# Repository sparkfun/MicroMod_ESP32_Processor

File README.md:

SparkFun MicroMod ESP32 Processor Board
========================================

[*SparkFun MicroMod ESP32 Processor Board (16781)*](https://www.sparkfun.com/products/16781)

The MicroMod ESP32 Processor Board combines Espressif's ESP32 with our M.2 connector interface to bring a power-packed processor board into our MicroMod ecosystem. 

The ESP32 includes a laundry list of functionality, including the dual-core Tensilica LX6 microprocessor, 240MHz clock frequency, 520kB internal SRAM, integrated WiFi transceiver, and hardware accelerated encryption (AES, SHA2, ECC, RSA-4096). With this MicroMod processor board, you have access to 8 general use IO pins, dedicated analog, digital, and PWM pins, as well as all the fan favorites - SPI, I<sup>2</sup>C, UART, and SDIO. Add to that 16MB flash storage and sleep current of around 500&micro;A, and you've got a perfect storm of versatility. 

Grab yourself a SparkFun MicroMod ESP32 Processor Board and a compatible carrier board and get to hacking! 

Repository Contents
-------------------

* **/Documentation** - Data sheets, additional product information
* **/Hardware** - Eagle design files (.brd, .sch)
* **/Production** - Production panel files (.brd)

Documentation
--------------
* **[Hookup Guide](https://learn.sparkfun.com/tutorials/micromod-esp32-processor-board-hookup-guide)** - Basic hookup guide for the SparkFun MicroMod ESP32 Processor Board.
* **[Getting Started with MicroMod](https://learn.sparkfun.com/tutorials/getting-started-with-micromod)** - A tutorial to help you get started with the MicroMod Ecosystem. 
* **[Designing with MicroMod](https://learn.sparkfun.com/tutorials/designing-with-micromod)** - A tutorial to walk you through the specs of the MicroMod processor and carrier board as well as the basics of incorporating the MicroMod form factor into your own PCB designs.

License Information
-------------------

This product is _**open source**_! 

Please review the LICENSE.md file for license information. 

If you have any questions or concerns on licensing, please contact technical support on our [SparkFun forums](https://forum.sparkfun.com/viewforum.php?f=152).

Distributed as-is; no warranty is given.

- Your friends at SparkFun.

_<COLLABORATION CREDIT>_

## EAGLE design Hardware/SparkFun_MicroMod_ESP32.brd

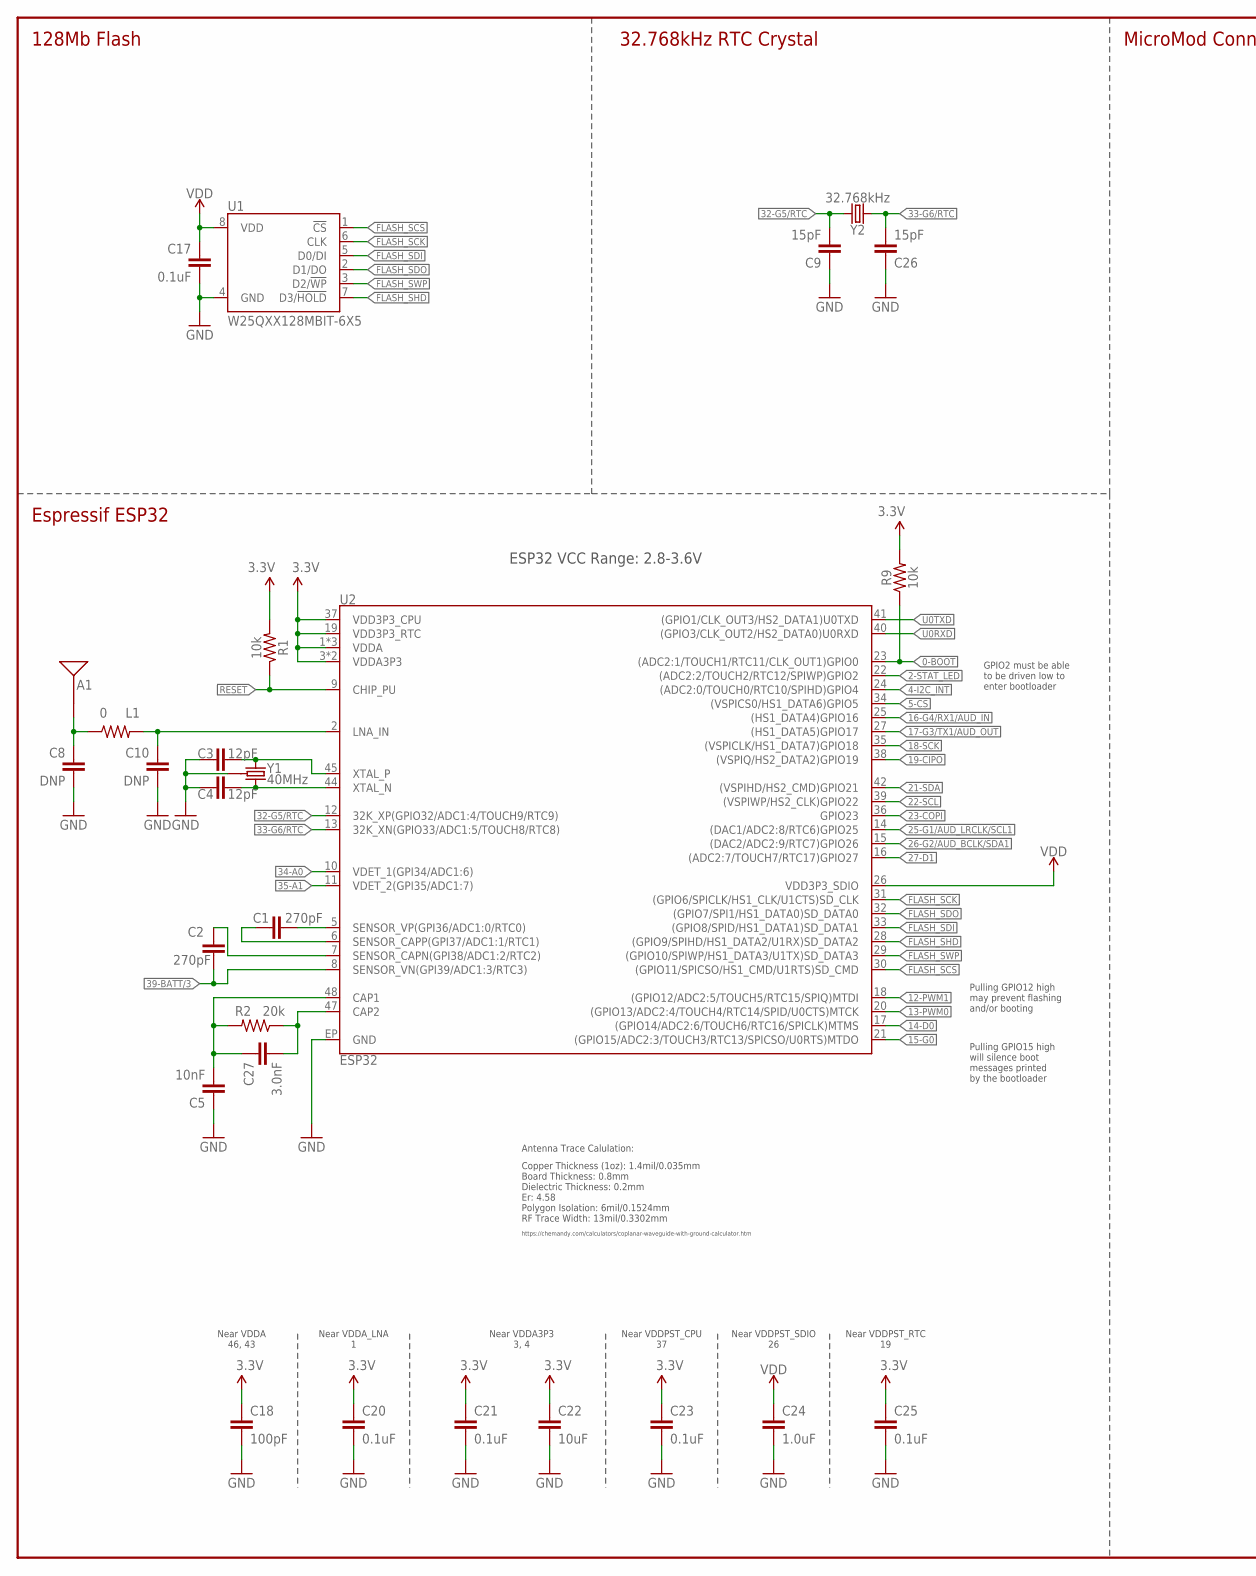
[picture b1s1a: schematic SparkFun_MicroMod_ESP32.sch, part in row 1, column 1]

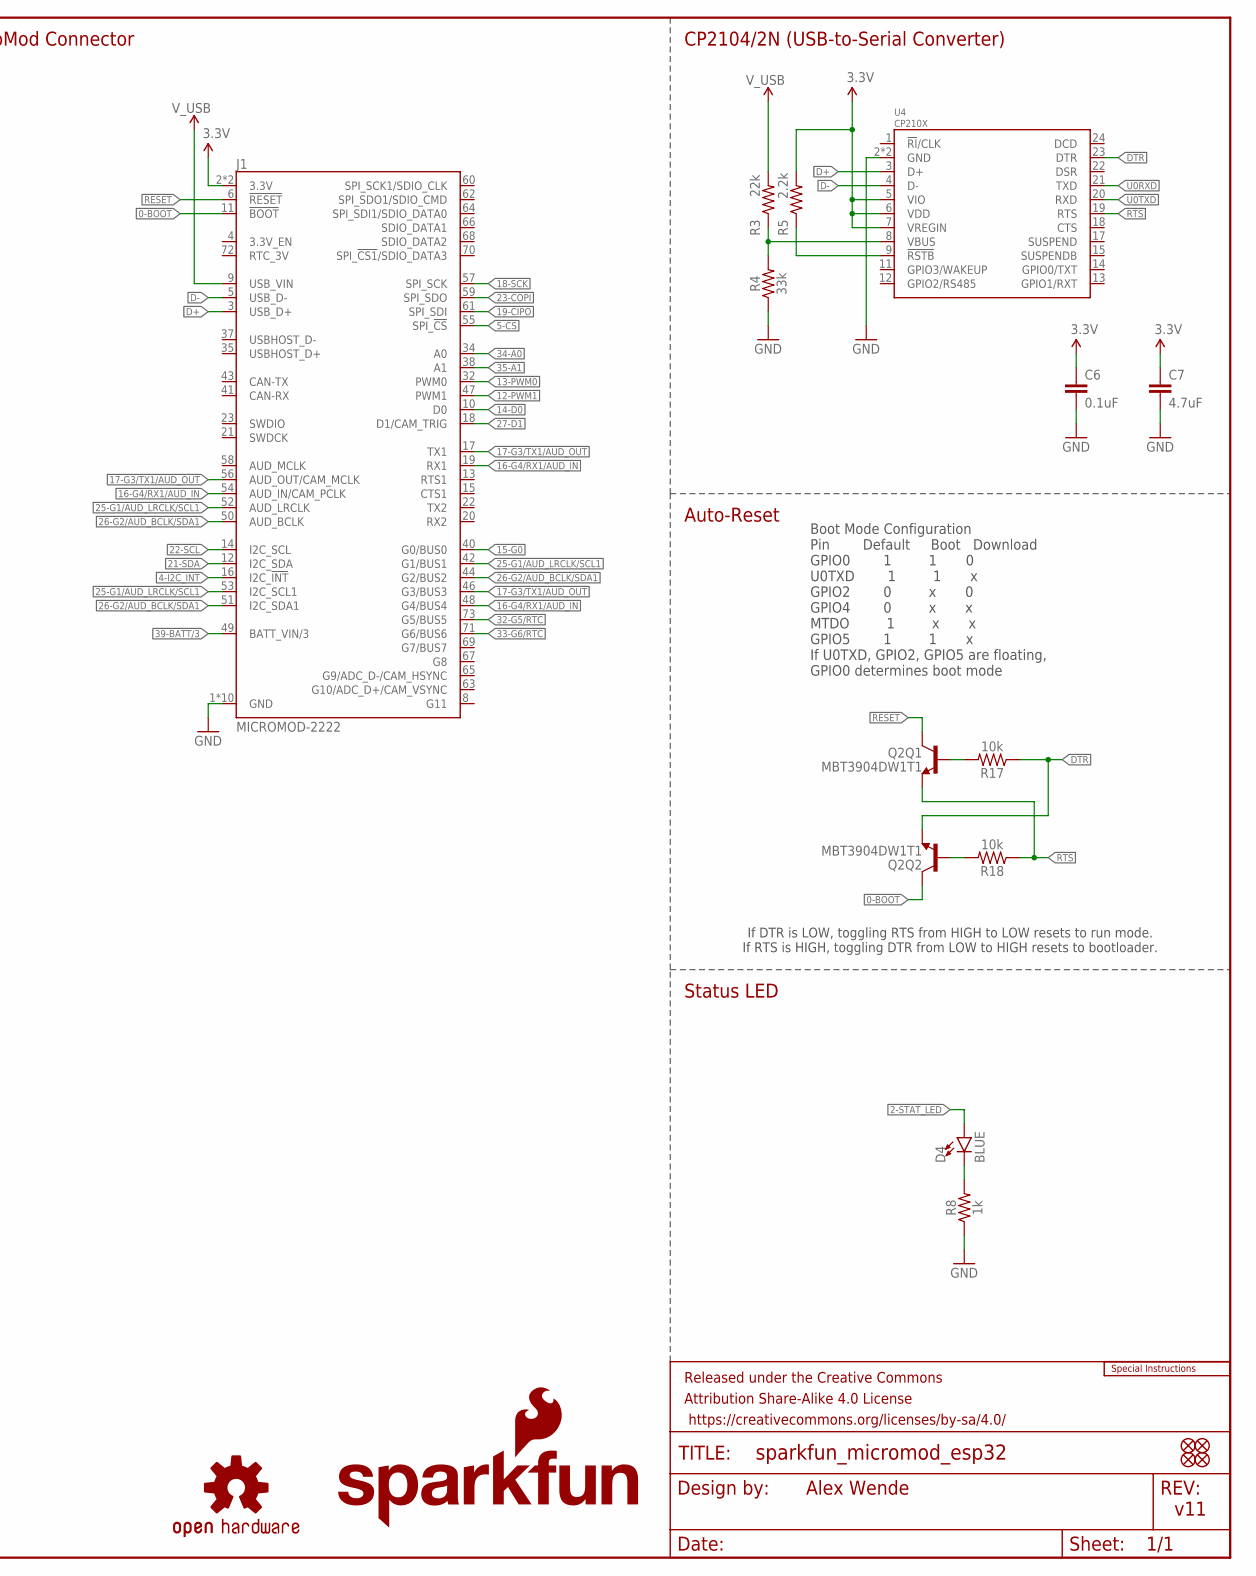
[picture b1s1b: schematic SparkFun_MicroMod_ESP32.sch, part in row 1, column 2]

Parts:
A1: ANTENNA2.4GHZ-8.0X1.0MM; ANT-2.4GHZ-8.0X1.0MM
C1, C2: 270pF; 0402-TIGHT
C3, C4: 12pF; 0402-TIGHT
C5: 10nF; 0402-TIGHT
C6, C17, C20, C21, C23, C25: 0.1uF; 0402-TIGHT
C7: 4.7uF; 0402-TIGHT
C8, C10: DNP; 0402-TIGHT
C9, C26: 15pF; 0402-TIGHT
C18: 100pF; 0402-TIGHT
C22: 10uF; 0402-TIGHT
C24: 1.0uF; 0402-TIGHT
C27: 3.0nF; 0402-TIGHT
D4: BLUE; LED-0603
FD1, FD2, FD3, FD4: FIDUCIALUFIDUCIAL; FIDUCIAL-MICRO
FRAME1: FRAME-LEDGER; CREATIVE_COMMONS
J1: MICROMOD-2222; M.2-CARD-E-22
L1: 0; 0402-TIGHT
LOGO1: SPECIAL_INSTRUCTIONS-ORDERING; ORDERING_INSTRUCTIONS
LOGO2: SFE_LOGO_NAME_FLAME.1_INCH; SFE_LOGO_NAME_FLAME_.1
LOGO3: OSHW-LOGOS; OSHW-LOGO-S
Q2: MBT3904DW1T1; SC70-6
R1, R9, R17, R18: 10k; 0402-TIGHT
R2: 20k; 0402-TIGHT
R3: 22k; 0402-TIGHT
R4: 33k; 0402-TIGHT
R5: 2.2k; 0402-TIGHT
R8: 1k; 0402-TIGHT
U1: W25QXX128MBIT-6X5; WSON-8-6X5
U2: ESP32; QFN48-0.4MM
U4: CP210X; QFN24
Y1: 40MHz; CRYSTAL-SMD-2X2.5MM
Y2: 32.768kHz; CRYSTAL-SMD-3.2X1.5MM

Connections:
0-!BOOT!: J1.11 (!BOOT!), Q2.6 (C), R9.1, U2.23 ((ADC2:1/TOUCH1/RTC11/CLK_OUT1)GPIO0)
2-STAT_LED: D4.A, U2.22 ((ADC2:2/TOUCH2/RTC12/SPIWP)GPIO2)
3.3V: C6.1, C7.1, C18.1, C20.1, C21.1, C22.1, C23.1, C25.1, J1.2 (3.3V), J1.74 (3.3V), R1.2, R5.2, R9.2, U2.1 (VDDA), U2.3 (VDDA3P3), U2.4 (VDDA3P3), U2.19 (VDD3P3_RTC), U2.37 (VDD3P3_CPU), U2.43 (VDDA), U2.46 (VDDA), U4.5 (VIO), U4.6 (VDD), U4.7 (VREGIN)
4-I2C_!INT: J1.16 (I2C_!INT!), U2.24 ((ADC2:0/TOUCH0/RTC10/SPIHD)GPIO4)
5-!CS: J1.55 (SPI_!CS!), U2.34 ((VSPICS0/HS1_DATA6)GPIO5)
12-PWM1: J1.47 (PWM1), U2.18 ((GPIO12/ADC2:5/TOUCH5/RTC15/SPIQ)MTDI)
13-PWM0: J1.32 (PWM0), U2.20 ((GPIO13/ADC2:4/TOUCH4/RTC14/SPID/U0CTS)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)
14-D0: J1.10 (D0), U2.17 ((GPIO14/ADC2:6/TOUCH6/RTC16/SPICLK)MTMS)
15-G0: J1.40 (G0/BUS0), U2.21 ((GPIO15/ADC2:3/TOUCH3/RTC13/SPICSO/U0RT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)
16-G4/RX1/AUD_IN: J1.19 (RX1), J1.48 (G4/BUS4), J1.54 (AUD_IN/CAM_PCLK), U2.25 ((HS1_DATA4)GPIO16)
17-G3/TX1/AUD_OUT: J1.17 (TX1), J1.46 (G3/BUS3), J1.56 (AUD_OUT/CAM_MCLK), U2.27 ((HS1_DATA5)GPIO17)
18-SCK: J1.57 (SPI_SCK), U2.35 ((VSPICLK/HS1_DATA7)GPIO18)
19-CIPO: J1.61 (SPI_SDI), U2.38 ((VSPIQ/HS2_DATA2)GPIO19)
21-SDA: J1.12 (I2C_SDA), U2.42 ((VSPIHD/HS2_CMD)GPIO21)
22-SCL: J1.14 (I2C_SCL), U2.39 ((VSPIWP/HS2_CLK)GPIO22)
23-COPI: J1.59 (SPI_SDO), U2.36 (GPIO23)
25-G1/AUD_LRCLK/SCL1: J1.42 (G1/BUS1), J1.52 (AUD_LRCLK), J1.53 (I2C_SCL1), U2.14 ((DAC1/ADC2:8/RTC6)GPIO25)
26-G2/AUD_BCLK/SDA1: J1.44 (G2/BUS2), J1.50 (AUD_BCLK), J1.51 (I2C_SDA1), U2.15 ((DAC2/ADC2:9/RTC7)GPIO26)
27-D1: J1.18 (D1/CAM_TRIG), U2.16 ((ADC2:7/TOUCH7/RTC17)GPIO27)
32-G5/RTC: C9.2, J1.73 (G5/BUS5), U2.12 (32K_XP(GPIO32/ADC1:4/TOUCH9/RTC9)), Y2.P$1 (1)
33-G6/RTC: C26.2, J1.71 (G6/BUS6), U2.13 (32K_XN(GPIO33/ADC1:5/TOUCH8/RTC8)), Y2.P$2 (2)
34-A0: J1.34 (A0), U2.10 (VDET_1(GPI34/ADC1:6))
35-A1: J1.38 (A1), U2.11 (VDET_2(GPI35/ADC1:7))
36: C1.2, U2.5 (SENSOR_VP(GPI36/ADC1:0/RTC0))
37: C1.1, U2.6 (SENSOR_CAPP(GPI37/ADC1:1/RTC1))
38: C2.1, U2.7 (SENSOR_CAPN(GPI38/ADC1:2/RTC2))
39-BATT/3: C2.2, J1.49 (BATT_VIN/3), U2.8 (SENSOR_VN(GPI39/ADC1:3/RTC3))
!RESET: J1.6 (!RESET!), Q2.3 (C), R1.1, U2.9 (CHIP_PU)
CAP_10N: C5.2, C27.1, R2.2, U2.48 (CAP1)
D+: J1.3 (USB_D+), U4.3 (D+)
D-: J1.5 (USB_D-), U4.4 (D-)
DTR: Q2.1 (E), R17.1, U4.23 (DTR)
FLASH_SCK: U1.6 (CLK), U2.31 ((GPIO6/SPICLK/HS1_CLK/U1CTS)SD_CLK)
FLASH_SCS: U1.1 (!CS!), U2.30 ((GPIO11/SPICSO/HS1_CMD/U1RTS)SD_CMD)
FLASH_SDI: U1.5 (D0/DI), U2.33 ((GPIO8/SPID/HS1_DATA1)SD_DATA1)
FLASH_SDO: U1.2 (D1/DO), U2.32 ((GPIO7/SPI1/HS1_DATA0)SD_DATA0)
FLASH_SHD: U1.7 (D3/!HOLD!), U2.28 ((GPIO9/SPIHD/HS1_DATA2/U1RX)SD_DATA2)
FLASH_SWP: U1.3 (D2/!WP!), U2.29 ((GPIO10/SPIWP/HS1_DATA3/U1TX)SD_DATA3)
GND: C3.1, C4.1, C5.1, C6.2, C7.2, C8.2, C9.1, C10.2, C17.2, C18.2, C20.2, C21.2, C22.2, C23.2, C24.2, C25.2, C26.1, J1.1 (GND), J1.7 (GND), J1.33 (GND), J1.36 (GND), J1.39 (GND), J1.45 (GND), J1.75 (GND), J1.GND1 (GND), J1.GND2 (GND), J1.GND3 (GND), R4.1, R8.1, U1.4 (GND), U2.EP (GND), U4.2 (GND), U4.PAD (GND), Y1.P2 (GND), Y1.P4 (GND)
unnamed: D4.C, R8.2
unnamed: R3.1, R4.2, U4.8 (VBUS)
unnamed: R5.1, U4.9 (!RSTB)
unnamed: C27.2, R2.1, U2.47 (CAP2)
unnamed: A1.FEED, C8.1, L1.1
unnamed: C10.1, L1.2, U2.2 (LNA_IN)
unnamed: Q2.5 (B), R17.2
unnamed: Q2.2 (B), R18.2
unnamed: C3.2, U2.45 (XTAL_P), Y1.P1 (1)
unnamed: C4.2, U2.44 (XTAL_N), Y1.P3 (2)
RTS: Q2.4 (E), R18.1, U4.19 (RTS)
U0RXD: U2.40 ((GPIO3/CLK_OUT2/HS2_DATA0)U0RXD), U4.21 (TXD)
U0TXD: U2.41 ((GPIO1/CLK_OUT3/HS2_DATA1)U0TXD), U4.20 (RXD)
VDD: C17.1, C24.1, U1.8 (VDD), U2.26 (VDD3P3_SDIO)
V_USB: J1.9 (USB_VIN), R3.2

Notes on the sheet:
Boot Mode Configuration Pin Default Boot Download GPIO0 1 1 0 U0TXD 1 1 x GPIO2 0 x 0 GPIO4 0 x x MTDO 1 x x GPIO5 1 1 x If U0TXD, GPIO2, GPIO5 are floating, GPIO0 determines boot mode
Auto-Reset
Near VDDA 46, 43
Near VDDA_LNA 1
Near VDDA3P3 3, 4
Near VDDPST_CPU 37
Near VDDPST_SDIO 26
Near VDDPST_RTC 19
Espressif ESP32
128Mb Flash
32.768kHz RTC Crystal
Status LED
v11
Alex Wende
ESP32 VCC Range: 2.8-3.6V
If DTR is LOW, toggling RTS from HIGH to LOW resets to run mode. If RTS is HIGH, toggling DTR from LOW to HIGH resets to bootloader.
CP2104/2N (USB-to-Serial Converter)
MicroMod Connector
Antenna Trace Calulation:
Copper Thickness (1oz): 1.4mil/0.035mm Board Thickness: 0.8mm Dielectric Thickness: 0.2mm Er: 4.58 Polygon Isolation: 6mil/0.1524mm RF Trace Width: 13mil/0.3302mm
https://chemandy.com/calculators/coplanar-waveguide-with-ground-calculator.htm
GPIO2 must be able to be driven low to enter bootloader
Pulling GPIO12 high may prevent flashing and/or booting
Pulling GPIO15 high will silence boot messages printed by the bootloader

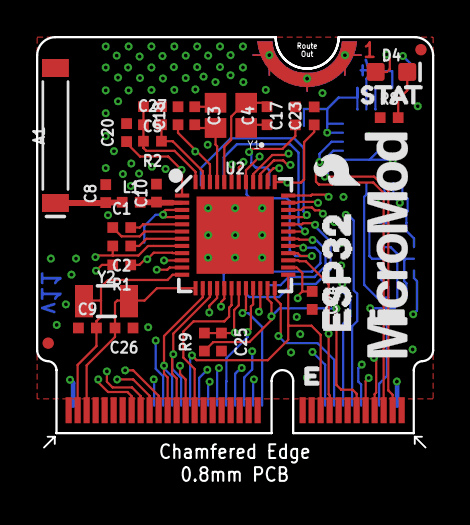
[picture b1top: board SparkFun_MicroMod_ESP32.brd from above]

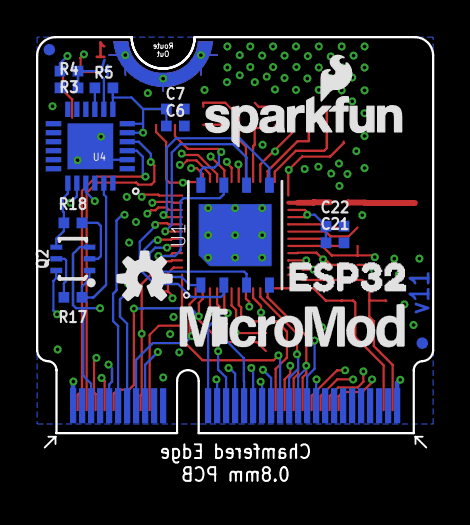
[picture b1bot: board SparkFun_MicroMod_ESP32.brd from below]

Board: 4 copper layers, 22.0 x 22.8 mm, 53 parts (18 on the bottom side), 54 nets.

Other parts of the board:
U$1: STAT0
U$2, U$6: MICROMOD_LOGO_.5
U$3, U$7: ESP321
U$4: SFE_LOGO_FLAME_.1

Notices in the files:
parts and their libraries:
SparkFun-RF: Licensing: Creative Commons ShareAlike 4.0 International - https://creativecommons.org/licenses/by-sa/4.0
SparkFun-Aesthetics: Released under the Creative Commons Attribution Share-Alike 4.0 License
SparkFun-Aesthetics: https://creativecommons.org/licenses/by-sa/4.0
